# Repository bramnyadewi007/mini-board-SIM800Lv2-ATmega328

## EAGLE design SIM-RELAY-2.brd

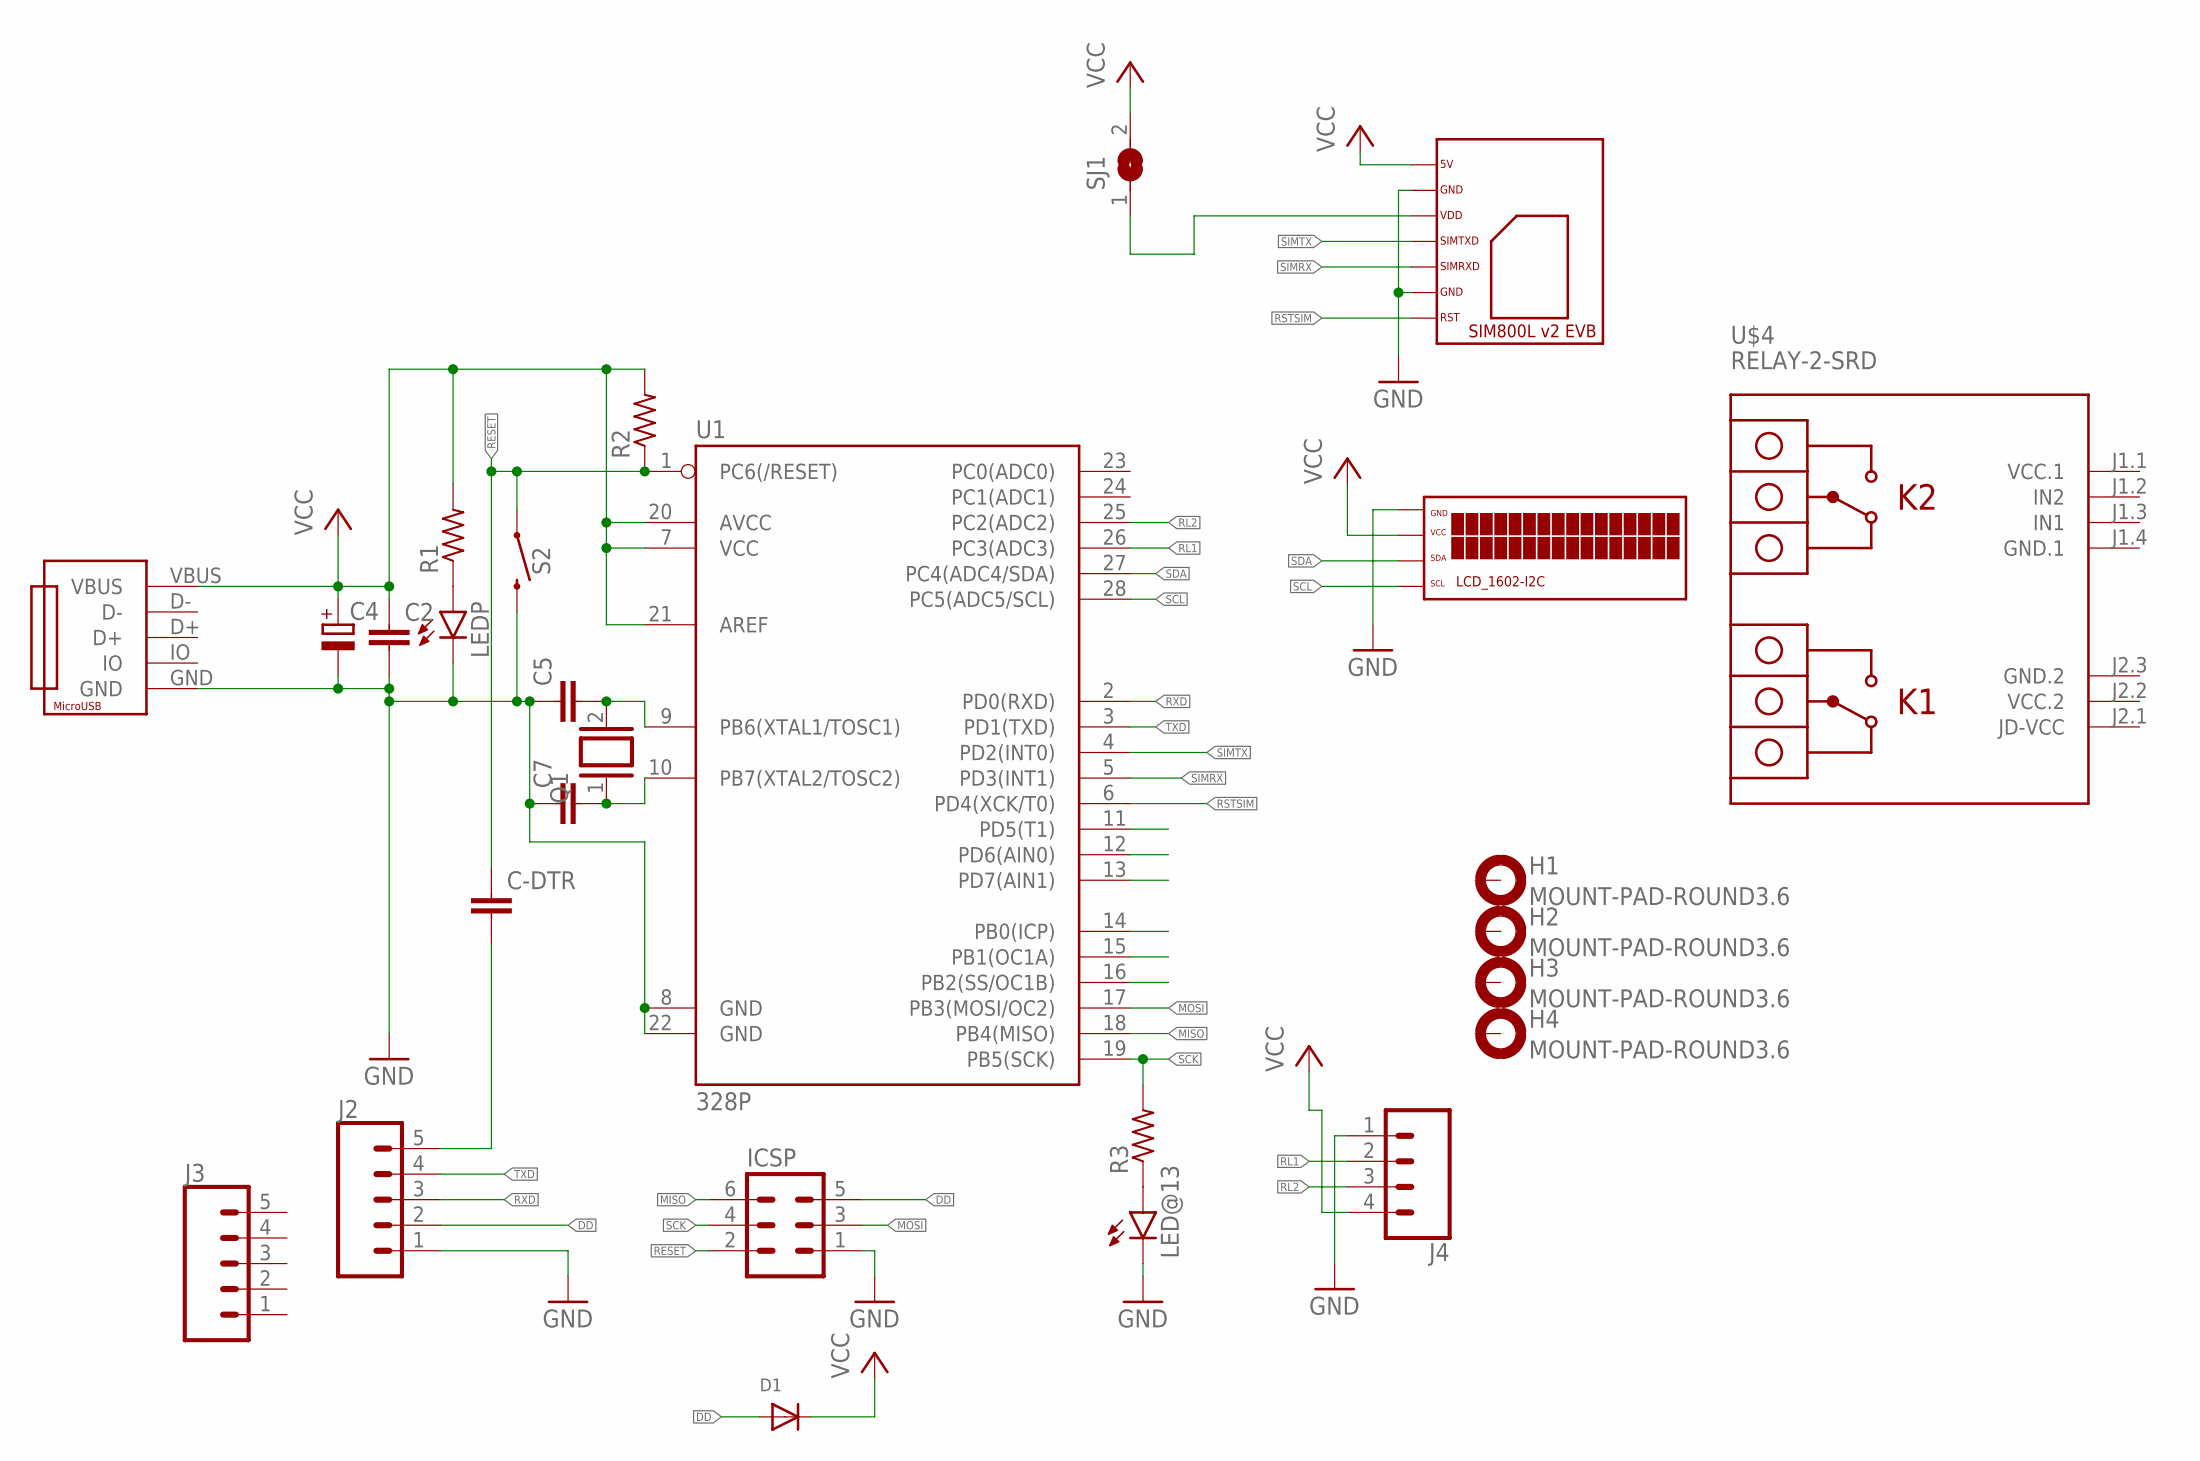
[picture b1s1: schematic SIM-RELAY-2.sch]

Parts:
C2: C-EU050-024X044; C050-024X044
C4: CPOL-EUB45181A; B45181A
C5, C7: C-EU025-024X044; C025-024X044
C-DTR: C-EU050-024X044; C050-024X044
D1: DIODESMA; SMADIODE
H1, H2, H3, H4: MOUNT-PAD-ROUND3.6; 3,6-PAD
ICSP: MA03-2
J2, J3: CONN_05; 1X05
J4: CONN_04POLAR; MOLEX-1X4
LED@13: LED3MM
LEDP: LED3MM
Q1: XTAL/S; QS
R1, R2, R3: R-US_R0805; R0805
S2: MOMENTARY-SWITCH-SPST-SMD-6.0X3.5MM; TACTILE_SWITCH_SMD_6.0X3.5MM
SJ1: SJ
U1: 328P; DIP28
U$1: LCD1602-I2C; 1602-I2C
U$2: SIM800V2
U$4: RELAY-2-SRD
U$5: MICROUSB-CONVERTER; MICROUSB-CONV-1

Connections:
DD: D1.A, ICSP.5, J2.2
GND: C2.2, C4.-, C5.1, C7.1, ICSP.1, J2.1, J4.1, LED@13.K (C), LEDP.K (C), S2.2, U1.8 (GND), U1.22 (GND), U$1.GND, U$2.GND, U$2.GND2, U$5.GND
GND.1: U$4.J1.4 (GND.1)
GND.2: U$4.J2.3 (GND.2)
MISO: ICSP.6, U1.18 (PB4(MISO))
MOSI: ICSP.3, U1.17 (PB3(MOSI/OC2))
unnamed: LEDP.A, R1.1
unnamed: LED@13.A, R3.1
unnamed: C-DTR.2, J2.5
unnamed: SJ1.1, U$2.VDD
unnamed: C7.2, Q1.1, U1.10 (PB7(XTAL2/TOSC2))
unnamed: C5.2, Q1.2, U1.9 (PB6(XTAL1/TOSC1))
RESET: C-DTR.1, ICSP.2, R2.1, S2.1, U1.1 (PC6(/RESET))
RL1: J4.2, U1.26 (PC3(ADC3))
RL2: J4.3, U1.25 (PC2(ADC2))
RSTSIM: U1.6 (PD4(XCK/T0)), U$2.RST
RXD: J2.3, U1.2 (PD0(RXD))
SCK: ICSP.4, R3.2, U1.19 (PB5(SCK))
SCL: U1.28 (PC5(ADC5/SCL)), U$1.SCL
SDA: U1.27 (PC4(ADC4/SDA)), U$1.SDA
SIMRX: U1.5 (PD3(INT1)), U$2.SIMRXD
SIMTX: U1.4 (PD2(INT0)), U$2.SIMTXD
TXD: J2.4, U1.3 (PD1(TXD))
VCC: C2.1, C4.+, D1.C, J4.4, R1.2, R2.2, SJ1.2, U1.7 (VCC), U1.20 (AVCC), U1.21 (AREF), U$1.VCC, U$2.5V, U$5.VBUS
VCC.1: U$4.J1.1 (VCC.1)
VCC.2: U$4.J2.2 (VCC.2)

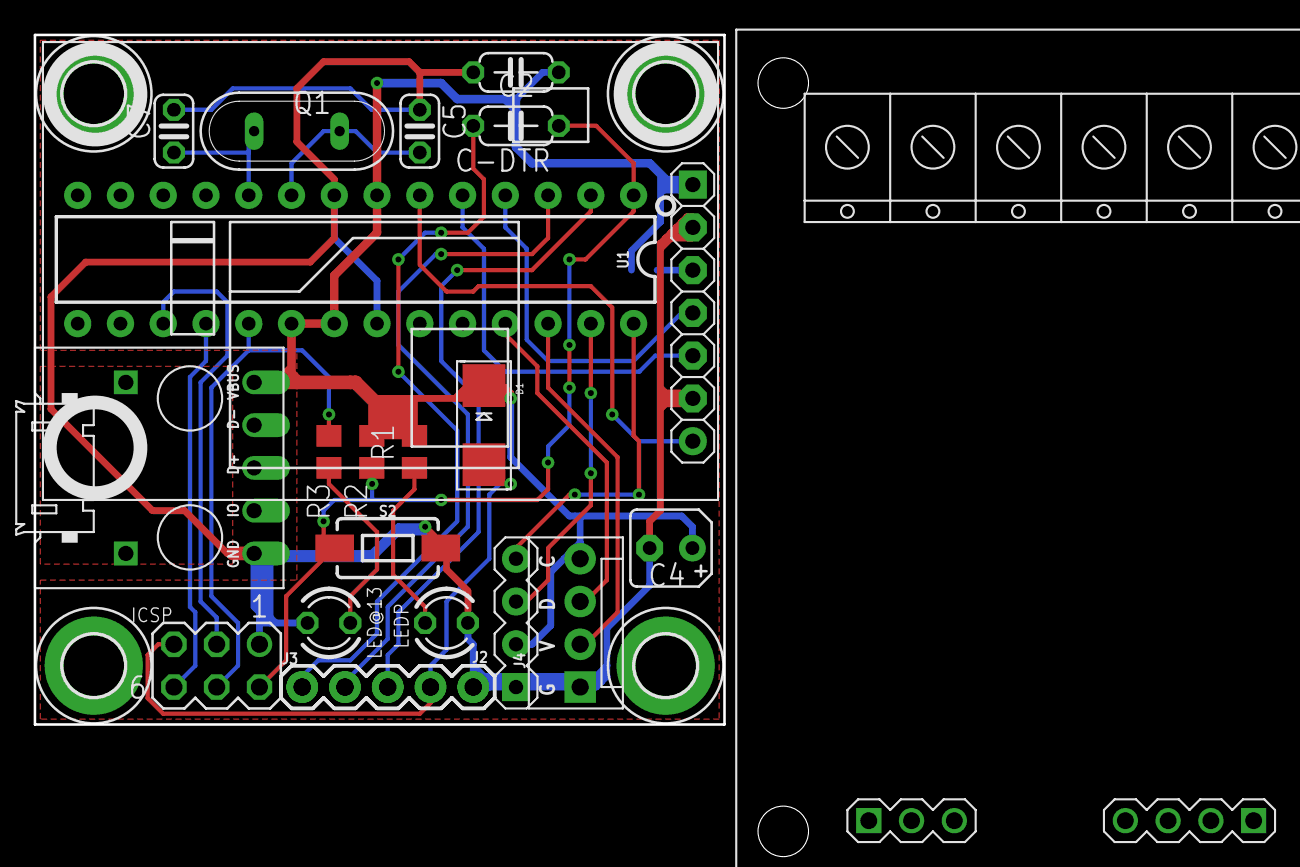
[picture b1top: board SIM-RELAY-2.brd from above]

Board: 2 copper layers, 41.0 x 41.0 mm, 27 parts (1 on the bottom side), 22 nets.

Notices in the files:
parts and their libraries:
SparkFun-IC-Microcontroller: Licensing: Creative Commons ShareAlike 4.0 International - https://creativecommons.org/licenses/by-sa/4.0
diy-modules: Released under the Creative Commons Attribution 4.0 International License: http://creativecommons.org/licenses/by/4.0
